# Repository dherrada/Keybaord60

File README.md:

# Keybaord60
A CircuitPython powered wireless gasket mount keyboard that accepts feather form-factor microcontrollers

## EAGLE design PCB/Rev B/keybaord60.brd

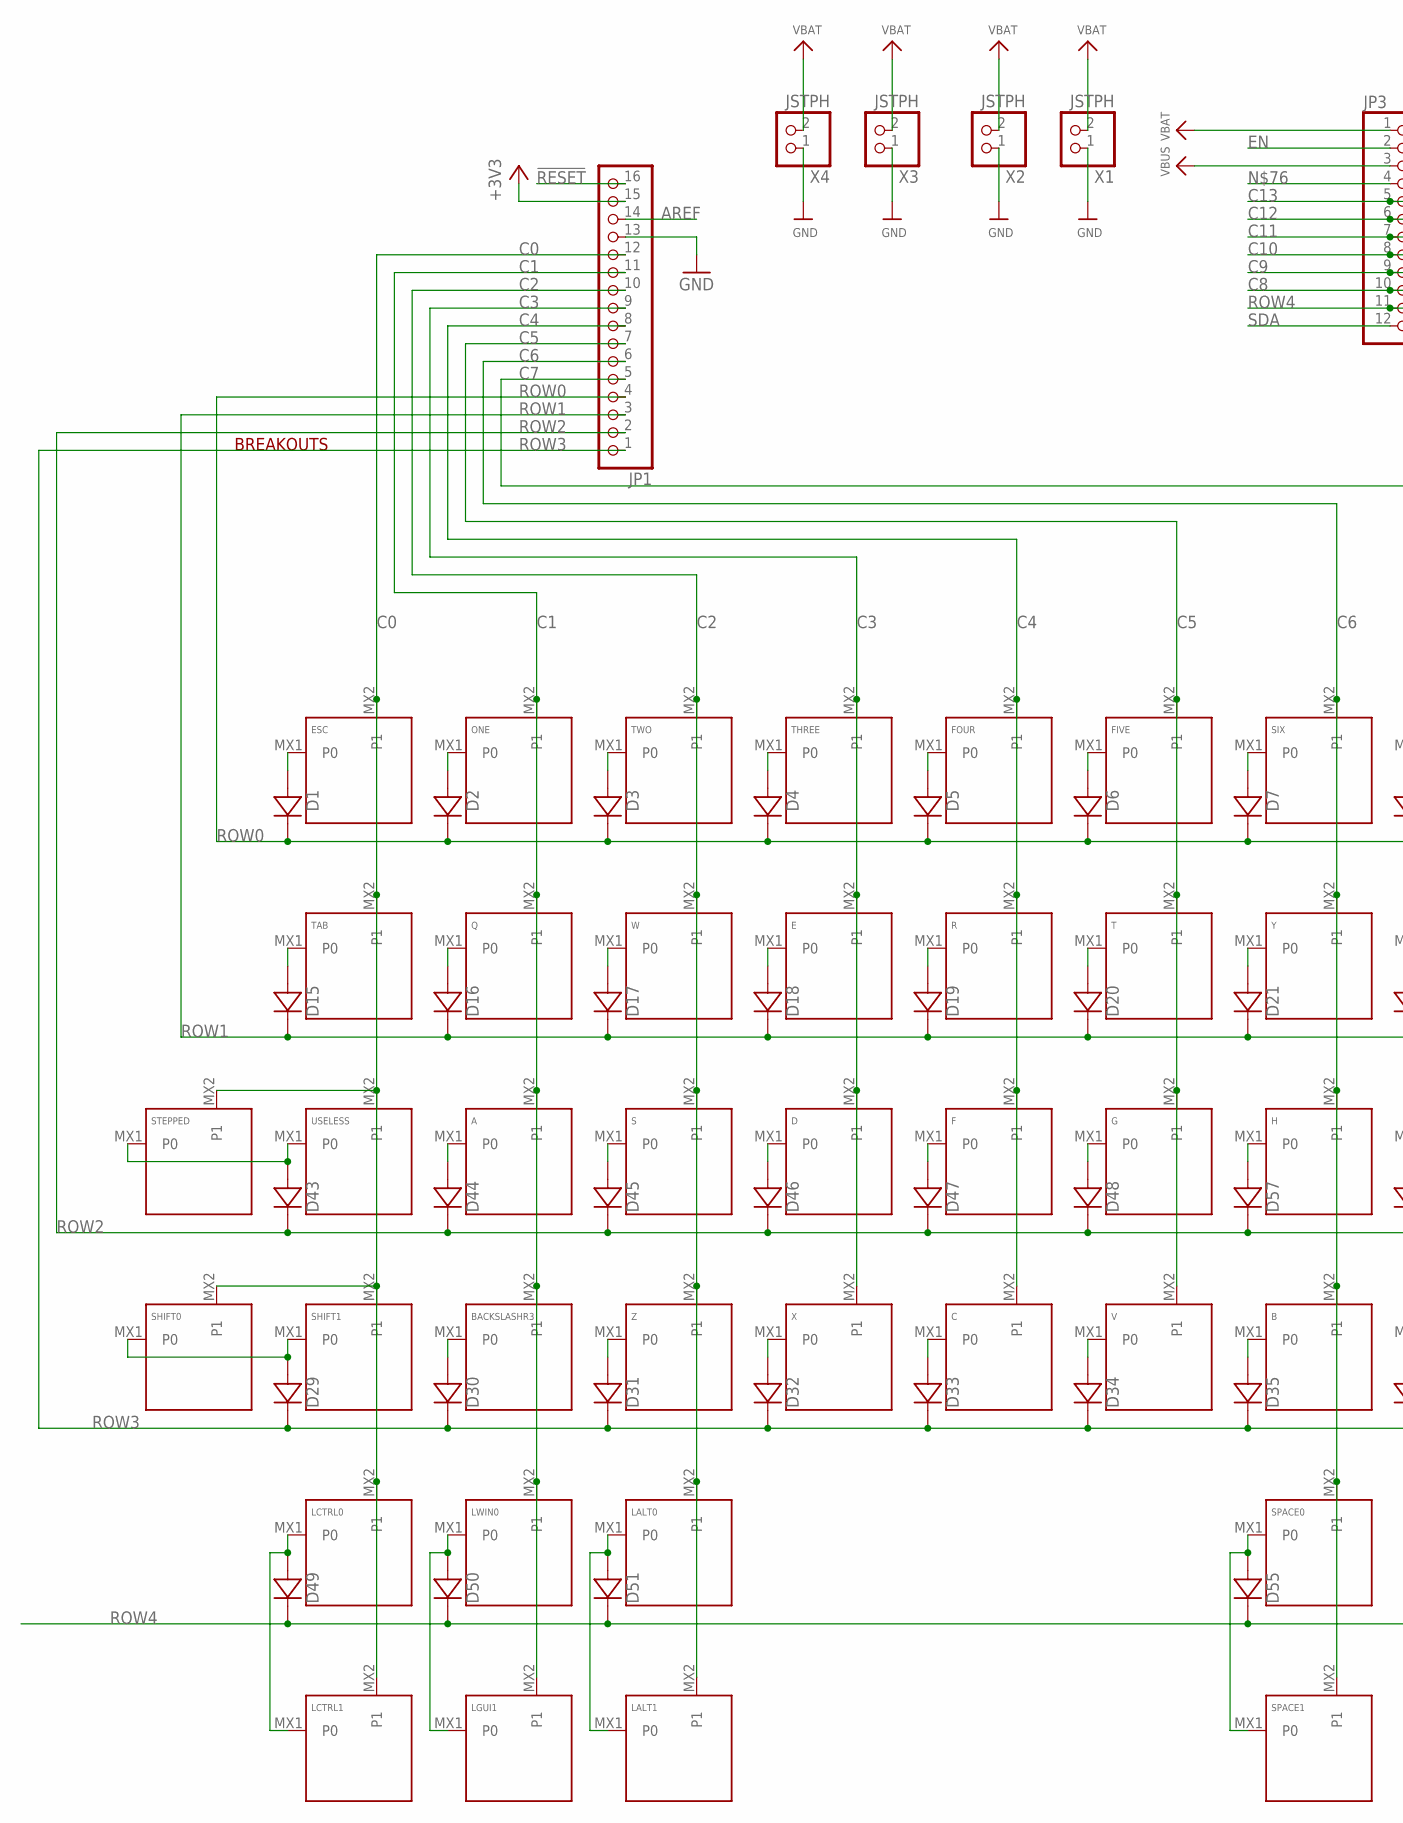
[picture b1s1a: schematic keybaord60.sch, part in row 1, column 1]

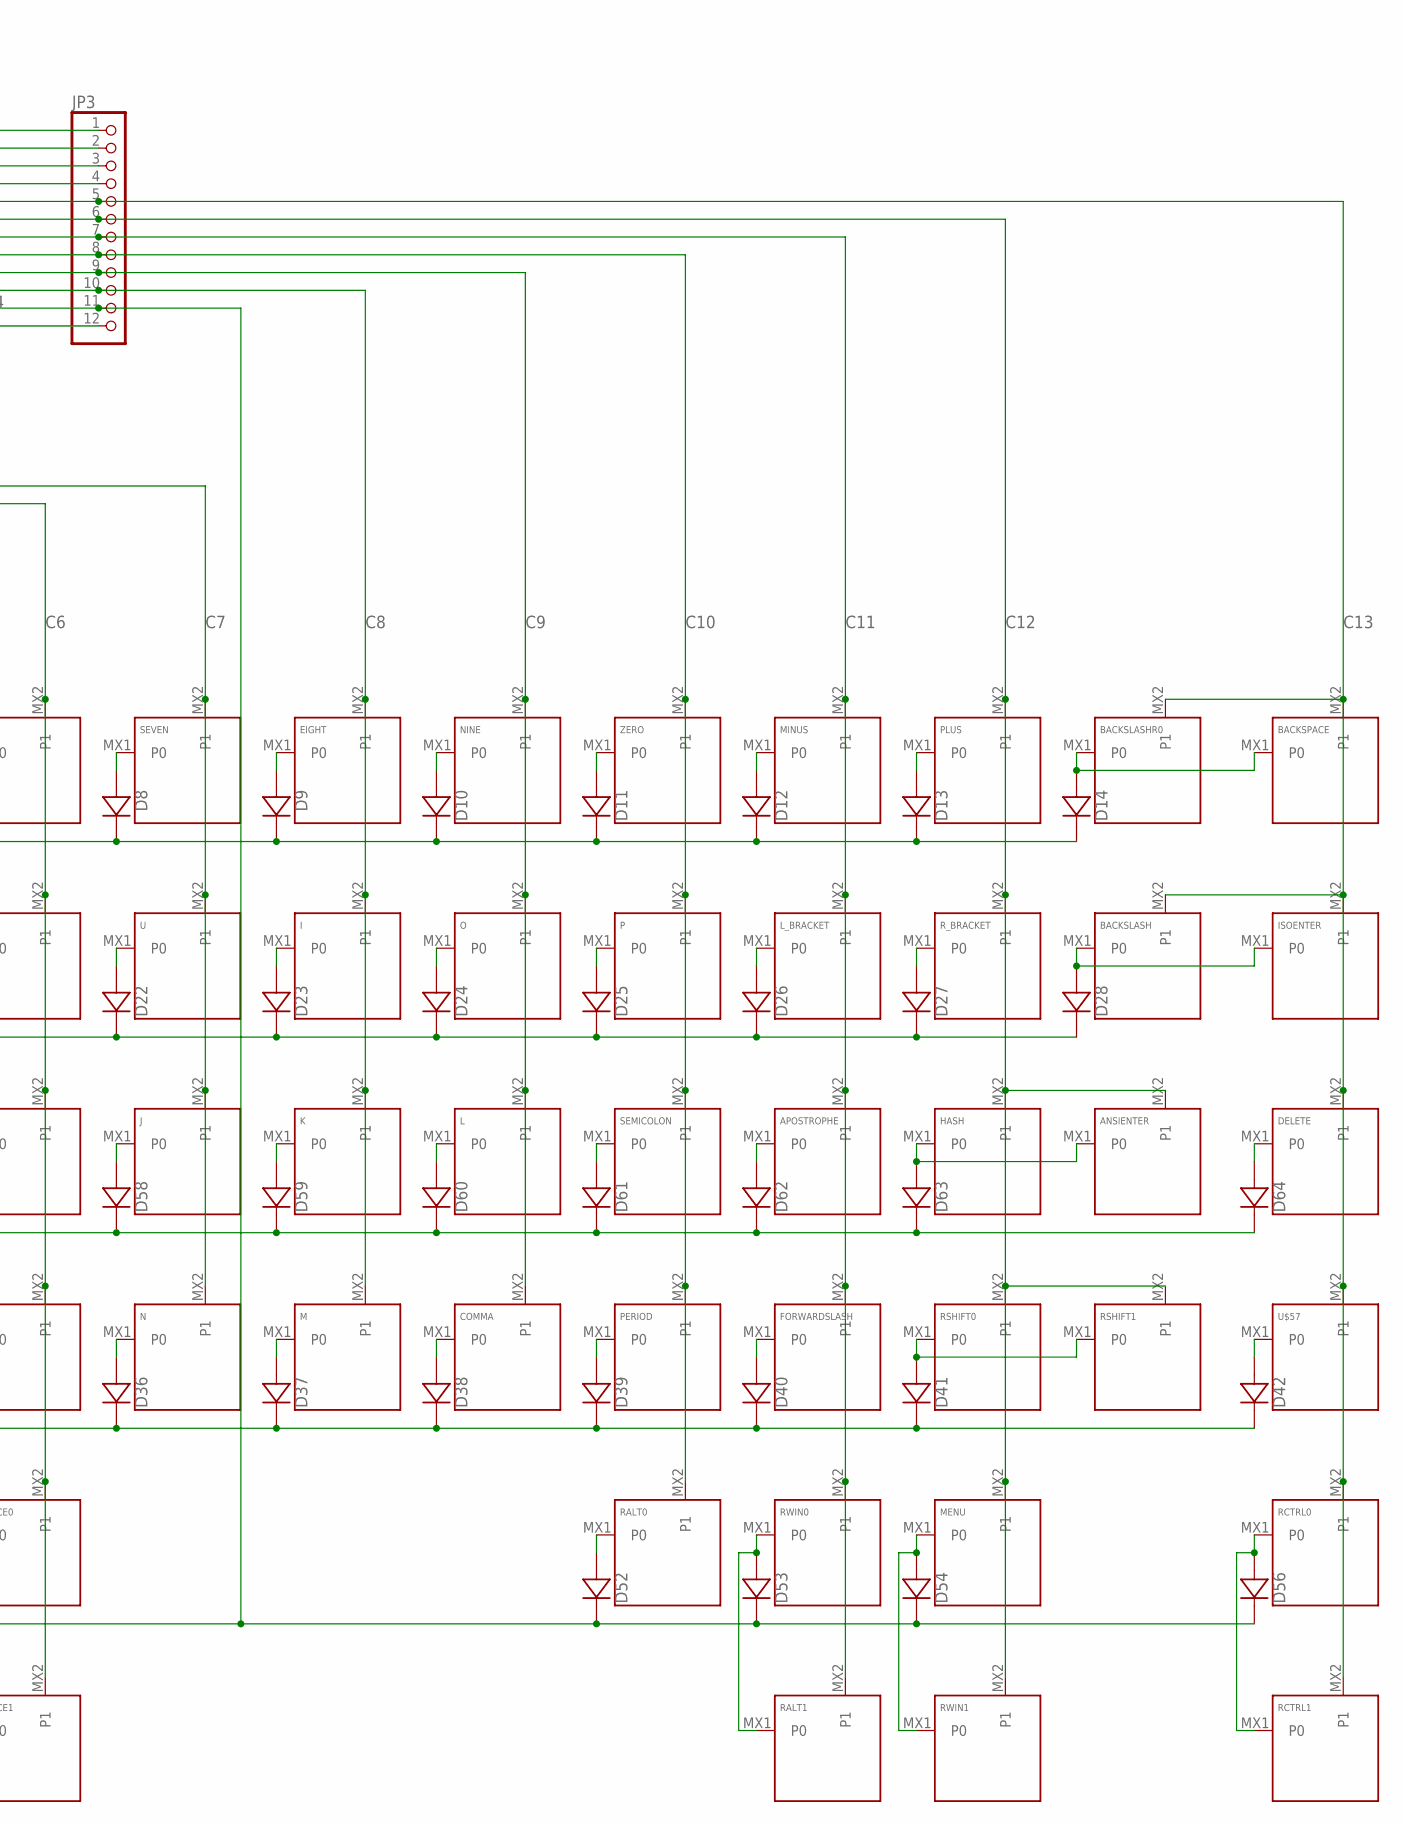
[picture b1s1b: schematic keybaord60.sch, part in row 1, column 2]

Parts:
A: KEYSWITCH-PLAIN-MX-1U; MX-1U
ANSIENTER: KEYSWITCH-PLAIN-MX-2U; MX-2U
APOSTROPHE: KEYSWITCH-PLAIN-MX-1U; MX-1U
B: KEYSWITCH-PLAIN-MX-1U; MX-1U
BACKSLASH: KEYSWITCH-PLAIN-MX-1U; MX-1U
BACKSLASHR0, BACKSLASHR3: KEYSWITCH-PLAIN-MX-1U; MX-1U
BACKSPACE: KEYSWITCH-PLAIN-MX-2U; MX-2U
C: KEYSWITCH-PLAIN-MX-1U; MX-1U
COMMA: KEYSWITCH-PLAIN-MX-1U; MX-1U
D: KEYSWITCH-PLAIN-MX-1U; MX-1U
D1, D2, D3, D4, D5, D6, D7, D8, D9, D10, D11, D12, D13, D14, D15, D16, D17, D18, D19, D20, D21, D22, D23, D24, D25, D26, D27, D28, D29, D30, D31, D32, D33, D34, D35, D36, D37, D38, D39, D40, D41, D42, D43, D44, D45, D46, D47, D48, D49, D50, D51, D52, D53, D54, D55, D56, D57, D58, D59, D60, D61, D62, D63, D64: DIODE-SOD-123; SOD-123
DELETE: KEYSWITCH-PLAIN-MX-1U; MX-1U
E: KEYSWITCH-PLAIN-MX-1U; MX-1U
EIGHT: KEYSWITCH-PLAIN-MX-1U; MX-1U
ESC: KEYSWITCH-PLAIN-MX-1U; MX-1U
F: KEYSWITCH-PLAIN-MX-1U; MX-1U
FIVE: KEYSWITCH-PLAIN-MX-1U; MX-1U
FORWARDSLASH: KEYSWITCH-PLAIN-MX-1U; MX-1U
FOUR: KEYSWITCH-PLAIN-MX-1U; MX-1U
G: KEYSWITCH-PLAIN-MX-1U; MX-1U
H: KEYSWITCH-PLAIN-MX-1U; MX-1U
HASH: KEYSWITCH-PLAIN-MX-1U; MX-1U
I: KEYSWITCH-PLAIN-MX-1U; MX-1U
ISOENTER: KEYSWITCH-PLAIN-MX-2U-ROTATED; MX-2U-ROTATED
J: KEYSWITCH-PLAIN-MX-1U; MX-1U
JP1: HEADER-1X16ROUND; 1X16_ROUND
JP3: HEADER-1X12; 1X12_ROUND
K: KEYSWITCH-PLAIN-MX-1U; MX-1U
L: KEYSWITCH-PLAIN-MX-1U; MX-1U
LALT0, LALT1: KEYSWITCH-PLAIN-MX-1U; MX-1U
LCTRL0, LCTRL1: KEYSWITCH-PLAIN-MX-1U; MX-1U
LGUI1: KEYSWITCH-PLAIN-MX-1U; MX-1U
LWIN0: KEYSWITCH-PLAIN-MX-1U; MX-1U
L_BRACKET: KEYSWITCH-PLAIN-MX-1U; MX-1U
M: KEYSWITCH-PLAIN-MX-1U; MX-1U
MENU: KEYSWITCH-PLAIN-MX-1U; MX-1U
MINUS: KEYSWITCH-PLAIN-MX-1U; MX-1U
N: KEYSWITCH-PLAIN-MX-1U; MX-1U
NINE: KEYSWITCH-PLAIN-MX-1U; MX-1U
O: KEYSWITCH-PLAIN-MX-1U; MX-1U
ONE: KEYSWITCH-PLAIN-MX-1U; MX-1U
P: KEYSWITCH-PLAIN-MX-1U; MX-1U
PERIOD: KEYSWITCH-PLAIN-MX-1U; MX-1U
PLUS: KEYSWITCH-PLAIN-MX-1U; MX-1U
Q: KEYSWITCH-PLAIN-MX-1U; MX-1U
R: KEYSWITCH-PLAIN-MX-1U; MX-1U
RALT0, RALT1: KEYSWITCH-PLAIN-MX-1U; MX-1U
RCTRL0, RCTRL1: KEYSWITCH-PLAIN-MX-1U; MX-1U
RSHIFT0: KEYSWITCH-PLAIN-MX-1U; MX-1U
RSHIFT1: KEYSWITCH-PLAIN-MX-2U; MX-2U
RWIN0, RWIN1: KEYSWITCH-PLAIN-MX-1U; MX-1U
R_BRACKET: KEYSWITCH-PLAIN-MX-1U; MX-1U
S: KEYSWITCH-PLAIN-MX-1U; MX-1U
SEMICOLON: KEYSWITCH-PLAIN-MX-1U; MX-1U
SEVEN: KEYSWITCH-PLAIN-MX-1U; MX-1U
SHIFT0: KEYSWITCH-PLAIN-MX-1U; MX-1U
SHIFT1: KEYSWITCH-PLAIN-MX-2U; MX-2U
SIX: KEYSWITCH-PLAIN-MX-1U; MX-1U
SPACE0: KEYSWITCH-PLAIN-MX-6.25U-FLIPPED; MX-6.25U-FLIPPED
SPACE1: KEYSWITCH-PLAIN-MX-7U-FLIPPED; MX-7U-FLIPPED
STEPPED: KEYSWITCH-PLAIN-MX-1U; MX-1U
T: KEYSWITCH-PLAIN-MX-1U; MX-1U
TAB: KEYSWITCH-PLAIN-MX-1U; MX-1U
THREE: KEYSWITCH-PLAIN-MX-1U; MX-1U
TWO: KEYSWITCH-PLAIN-MX-1U; MX-1U
U: KEYSWITCH-PLAIN-MX-1U; MX-1U
U$57: KEYSWITCH-PLAIN-MX-1U; MX-1U
USELESS: KEYSWITCH-PLAIN-MX-1U; MX-1U
V: KEYSWITCH-PLAIN-MX-1U; MX-1U
W: KEYSWITCH-PLAIN-MX-1U; MX-1U
X: KEYSWITCH-PLAIN-MX-1U; MX-1U
X1, X2, X3, X4: JSTPH; JSTPH2
Y: KEYSWITCH-PLAIN-MX-1U; MX-1U
Z: KEYSWITCH-PLAIN-MX-1U; MX-1U
ZERO: KEYSWITCH-PLAIN-MX-1U; MX-1U

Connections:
!RESET: JP1.16
+3V3: JP1.15
AREF: JP1.14
C0: ESC.MX2 (P1), JP1.12, LCTRL0.MX2 (P1), LCTRL1.MX2 (P1), SHIFT0.MX2 (P1), SHIFT1.MX2 (P1), STEPPED.MX2 (P1), TAB.MX2 (P1), USELESS.MX2 (P1)
C1: A.MX2 (P1), BACKSLASHR3.MX2 (P1), JP1.11, LGUI1.MX2 (P1), LWIN0.MX2 (P1), ONE.MX2 (P1), Q.MX2 (P1)
C2: JP1.10, LALT0.MX2 (P1), LALT1.MX2 (P1), S.MX2 (P1), TWO.MX2 (P1), W.MX2 (P1), Z.MX2 (P1)
C3: D.MX2 (P1), E.MX2 (P1), JP1.9, THREE.MX2 (P1), X.MX2 (P1)
C4: C.MX2 (P1), F.MX2 (P1), FOUR.MX2 (P1), JP1.8, R.MX2 (P1)
C5: FIVE.MX2 (P1), G.MX2 (P1), JP1.7, T.MX2 (P1), V.MX2 (P1)
C6: B.MX2 (P1), H.MX2 (P1), JP1.6, SIX.MX2 (P1), SPACE0.MX2 (P1), SPACE1.MX2 (P1), Y.MX2 (P1)
C7: J.MX2 (P1), JP1.5, N.MX2 (P1), SEVEN.MX2 (P1), U.MX2 (P1)
C8: EIGHT.MX2 (P1), I.MX2 (P1), JP3.10, K.MX2 (P1), M.MX2 (P1)
C9: COMMA.MX2 (P1), JP3.9, L.MX2 (P1), NINE.MX2 (P1), O.MX2 (P1)
C10: JP3.8, P.MX2 (P1), PERIOD.MX2 (P1), RALT0.MX2 (P1), SEMICOLON.MX2 (P1), ZERO.MX2 (P1)
C11: APOSTROPHE.MX2 (P1), FORWARDSLASH.MX2 (P1), JP3.7, L_BRACKET.MX2 (P1), MINUS.MX2 (P1), RALT1.MX2 (P1), RWIN0.MX2 (P1)
C12: ANSIENTER.MX2 (P1), HASH.MX2 (P1), JP3.6, MENU.MX2 (P1), PLUS.MX2 (P1), RSHIFT0.MX2 (P1), RSHIFT1.MX2 (P1), RWIN1.MX2 (P1), R_BRACKET.MX2 (P1)
C13: BACKSLASH.MX2 (P1), BACKSLASHR0.MX2 (P1), BACKSPACE.MX2 (P1), DELETE.MX2 (P1), ISOENTER.MX2 (P1), JP3.5, RCTRL0.MX2 (P1), RCTRL1.MX2 (P1), U$57.MX2 (P1)
EN: JP3.2
GND: JP1.13, X1.1, X2.1, X3.1, X4.1
unnamed: D1.A, ESC.MX1 (P0)
unnamed: D2.A, ONE.MX1 (P0)
unnamed: D3.A, TWO.MX1 (P0)
unnamed: D4.A, THREE.MX1 (P0)
unnamed: D5.A, FOUR.MX1 (P0)
unnamed: D6.A, FIVE.MX1 (P0)
unnamed: D7.A, SIX.MX1 (P0)
unnamed: D8.A, SEVEN.MX1 (P0)
unnamed: D9.A, EIGHT.MX1 (P0)
unnamed: D10.A, NINE.MX1 (P0)
unnamed: D11.A, ZERO.MX1 (P0)
unnamed: D12.A, MINUS.MX1 (P0)
unnamed: D13.A, PLUS.MX1 (P0)
unnamed: BACKSLASHR0.MX1 (P0), BACKSPACE.MX1 (P0), D14.A
unnamed: D15.A, TAB.MX1 (P0)
unnamed: D16.A, Q.MX1 (P0)
unnamed: D17.A, W.MX1 (P0)
unnamed: D18.A, E.MX1 (P0)
unnamed: D19.A, R.MX1 (P0)
unnamed: D20.A, T.MX1 (P0)
unnamed: D21.A, Y.MX1 (P0)
unnamed: D22.A, U.MX1 (P0)
unnamed: D23.A, I.MX1 (P0)
unnamed: D24.A, O.MX1 (P0)
unnamed: D25.A, P.MX1 (P0)
unnamed: D26.A, L_BRACKET.MX1 (P0)
unnamed: D27.A, R_BRACKET.MX1 (P0)
unnamed: BACKSLASH.MX1 (P0), D28.A, ISOENTER.MX1 (P0)
unnamed: D43.A, STEPPED.MX1 (P0), USELESS.MX1 (P0)
unnamed: A.MX1 (P0), D44.A
unnamed: D45.A, S.MX1 (P0)
unnamed: D.MX1 (P0), D46.A
unnamed: D47.A, F.MX1 (P0)
unnamed: D48.A, G.MX1 (P0)
unnamed: D57.A, H.MX1 (P0)
unnamed: D58.A, J.MX1 (P0)
unnamed: D59.A, K.MX1 (P0)
unnamed: D60.A, L.MX1 (P0)
unnamed: D61.A, SEMICOLON.MX1 (P0)
unnamed: APOSTROPHE.MX1 (P0), D62.A
unnamed: ANSIENTER.MX1 (P0), D63.A, HASH.MX1 (P0)
unnamed: D64.A, DELETE.MX1 (P0)
unnamed: D29.A, SHIFT0.MX1 (P0), SHIFT1.MX1 (P0)
unnamed: BACKSLASHR3.MX1 (P0), D30.A
unnamed: D31.A, Z.MX1 (P0)
unnamed: D32.A, X.MX1 (P0)
unnamed: C.MX1 (P0), D33.A
unnamed: D34.A, V.MX1 (P0)
unnamed: B.MX1 (P0), D35.A
unnamed: D36.A, N.MX1 (P0)
unnamed: D37.A, M.MX1 (P0)
unnamed: COMMA.MX1 (P0), D38.A
unnamed: D39.A, PERIOD.MX1 (P0)
unnamed: D40.A, FORWARDSLASH.MX1 (P0)
unnamed: D41.A, RSHIFT0.MX1 (P0), RSHIFT1.MX1 (P0)
unnamed: D42.A, U$57.MX1 (P0)
unnamed: D49.A, LCTRL0.MX1 (P0), LCTRL1.MX1 (P0)
unnamed: D50.A, LGUI1.MX1 (P0), LWIN0.MX1 (P0)
unnamed: D51.A, LALT0.MX1 (P0), LALT1.MX1 (P0)
unnamed: D52.A, RALT0.MX1 (P0)
unnamed: D53.A, RALT1.MX1 (P0), RWIN0.MX1 (P0)
unnamed: D54.A, MENU.MX1 (P0), RWIN1.MX1 (P0)
unnamed: D55.A, SPACE0.MX1 (P0), SPACE1.MX1 (P0)
unnamed: D56.A, RCTRL0.MX1 (P0), RCTRL1.MX1 (P0)
ROW0: D1.C, D2.C, D3.C, D4.C, D5.C, D6.C, D7.C, D8.C, D9.C, D10.C, D11.C, D12.C, D13.C, D14.C, JP1.4
ROW1: D15.C, D16.C, D17.C, D18.C, D19.C, D20.C, D21.C, D22.C, D23.C, D24.C, D25.C, D26.C, D27.C, D28.C, JP1.3
ROW2: D43.C, D44.C, D45.C, D46.C, D47.C, D48.C, D57.C, D58.C, D59.C, D60.C, D61.C, D62.C, D63.C, D64.C, JP1.2
ROW3: D29.C, D30.C, D31.C, D32.C, D33.C, D34.C, D35.C, D36.C, D37.C, D38.C, D39.C, D40.C, D41.C, D42.C, JP1.1
ROW4: D49.C, D50.C, D51.C, D52.C, D53.C, D54.C, D55.C, D56.C, JP3.11
SDA: JP3.12
VBAT: JP3.1, X1.2, X2.2, X3.2, X4.2
VBUS: JP3.3

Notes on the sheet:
BREAKOUTS

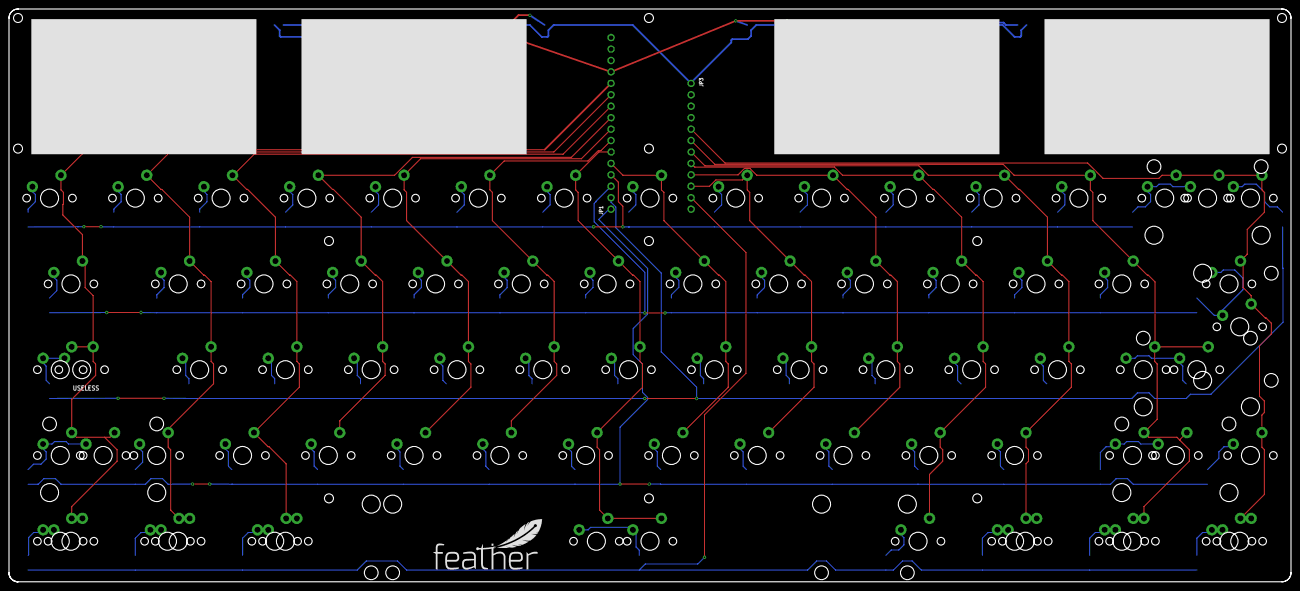
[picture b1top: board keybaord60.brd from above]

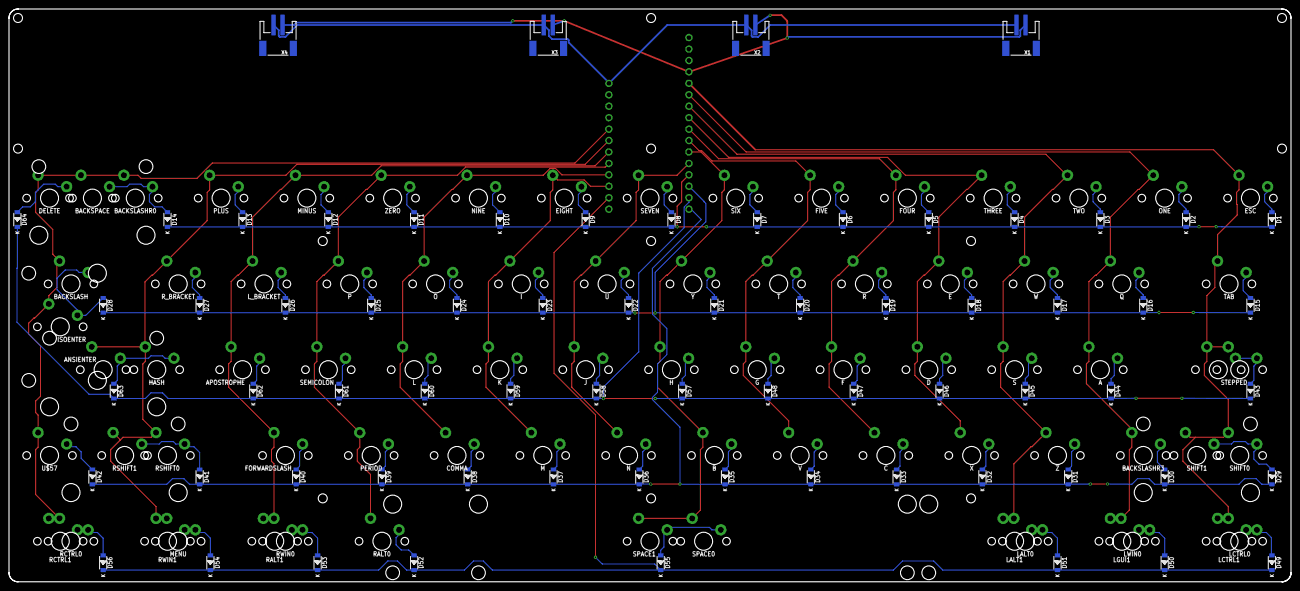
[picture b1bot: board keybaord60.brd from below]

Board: 2 copper layers, 284.7 x 127.2 mm, 148 parts (68 on the bottom side), 85 nets.

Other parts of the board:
U$1: FEATHERLOGO

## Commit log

2021-04-27 Case rev A and PCB rev B
2021-04-27 Added render
2021-04-27 Added image
2021-04-27 filetype
2021-04-27 CaPiTaLiZaTiOn
2021-04-27 Updated rev B, added pcb render
2021-04-27 Moved render
2021-04-27 Added pcb render

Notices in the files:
parts and their libraries:
microbuilder: This work is placed in the public domain, and may be freely used for commercial and non-commercial work with the following conditions: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
